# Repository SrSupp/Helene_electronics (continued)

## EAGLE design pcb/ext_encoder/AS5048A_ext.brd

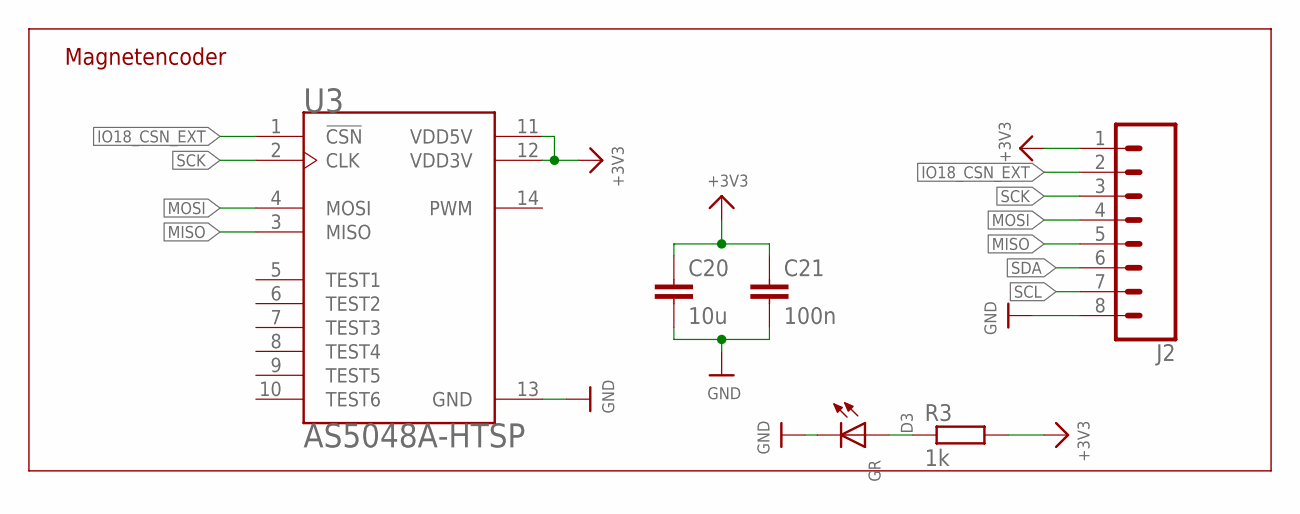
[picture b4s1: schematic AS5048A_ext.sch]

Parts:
C20: 10u; C0805
C21: 100n; C0805
D3: GR; CHIP-LED0805
J2: CONN_08BM08B-SRSS-TB; BM08B-SRSS-TB
R3: 1k; R0805
U3: AS5048A-HTSP; SOP65P640X120-14N

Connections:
+3V3: C20.1, C21.1, J2.1, R3.2, U3.11 (VDD5V), U3.12 (VDD3V)
GND: C20.2, C21.2, D3.C, J2.8, U3.13 (GND)
IO18_CSN_EXT: J2.2, U3.1 (!CSN)
MISO: J2.5, U3.3 (MISO)
MOSI: J2.4, U3.4 (MOSI)
unnamed: D3.A, R3.1
SCK: J2.3, U3.2 (CLK)
SCL: J2.7
SDA: J2.6

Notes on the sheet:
Magnetencoder

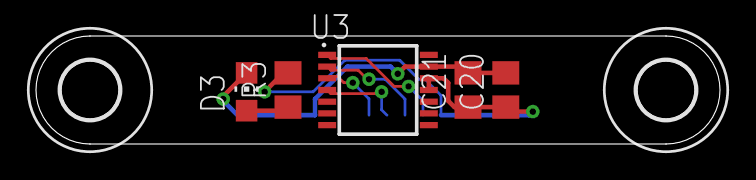
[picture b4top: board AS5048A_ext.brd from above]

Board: 2 copper layers, 38.0 x 6.0 mm, 8 parts (1 on the bottom side), 7 nets.

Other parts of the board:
U$1, U$2: 3,2

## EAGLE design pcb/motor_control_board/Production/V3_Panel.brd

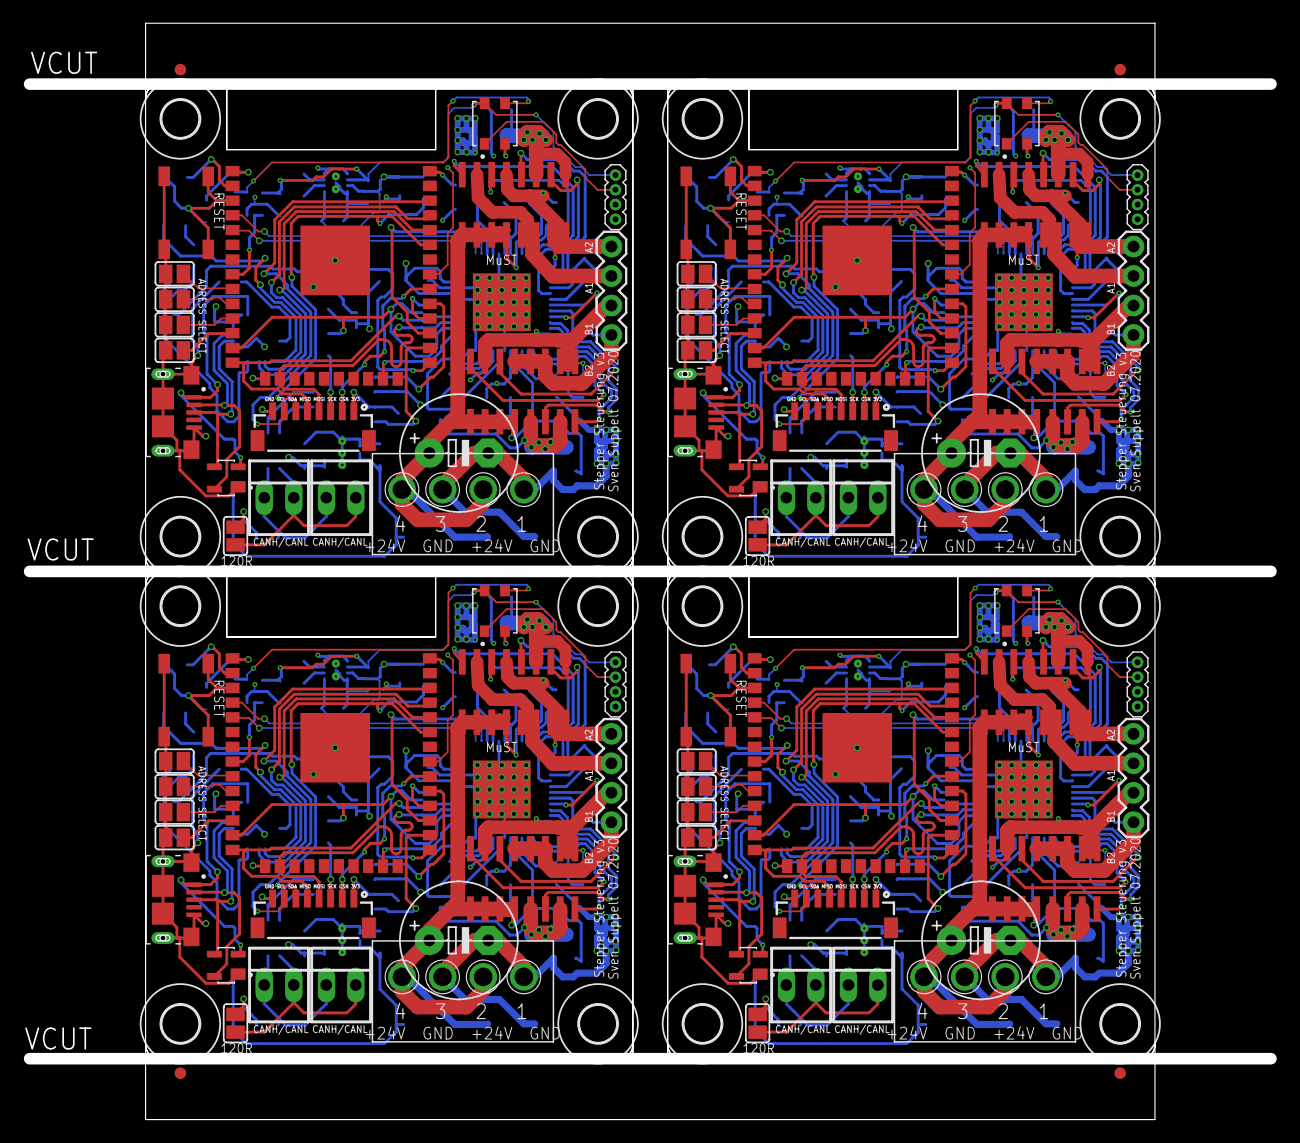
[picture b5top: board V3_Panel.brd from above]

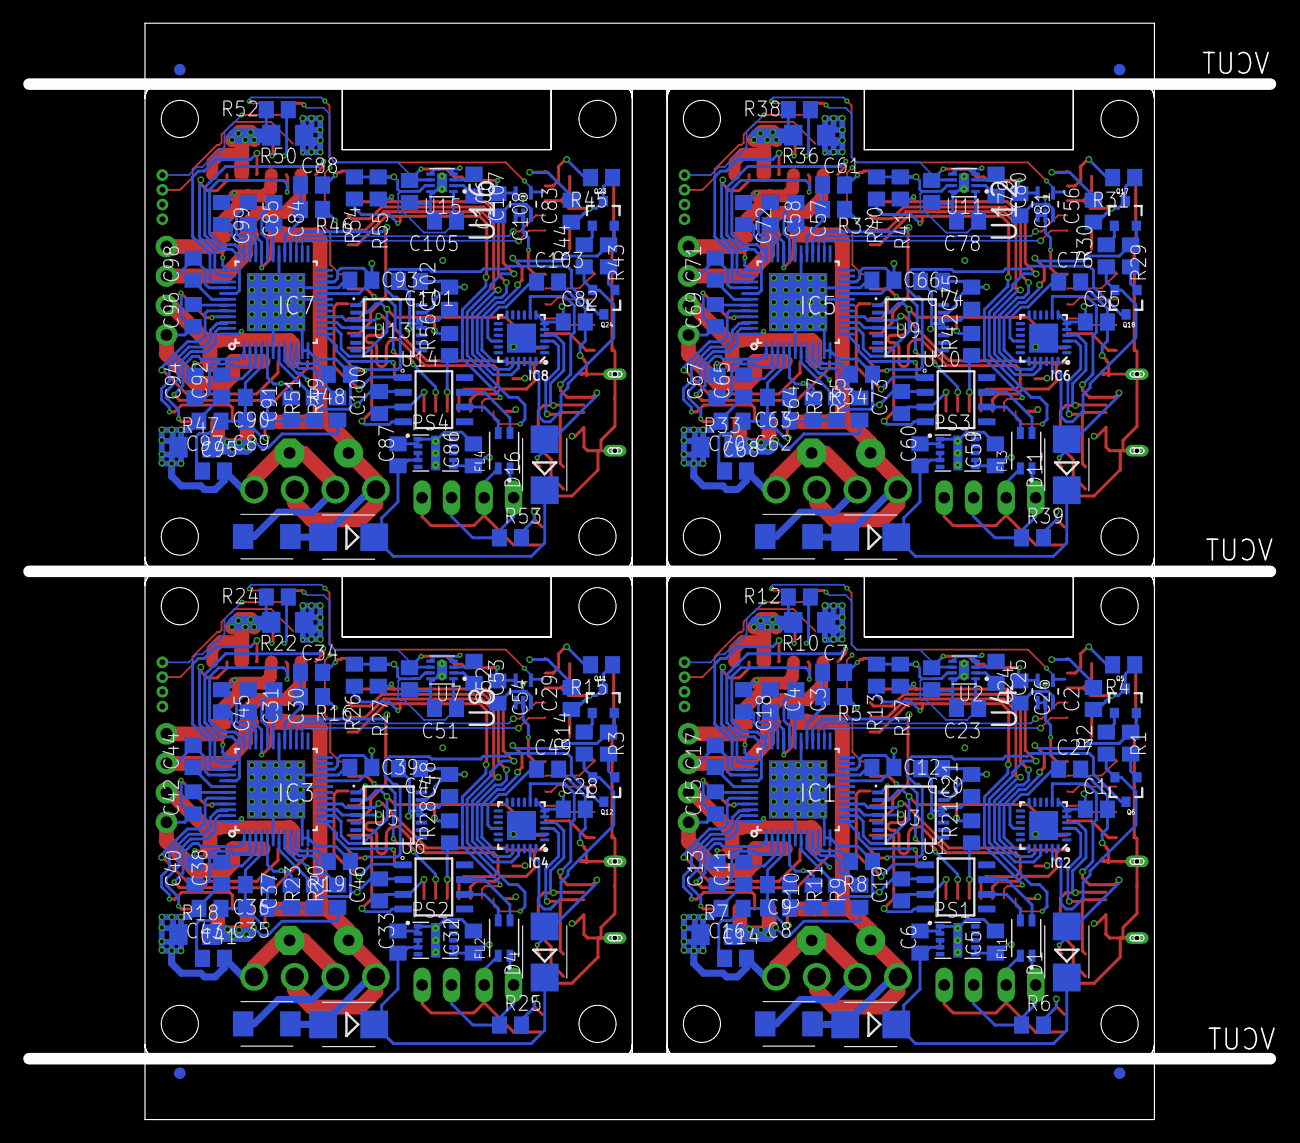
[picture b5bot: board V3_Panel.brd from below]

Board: 4 copper layers, 107.0 x 93.5 mm, 320 parts (216 on the bottom side), 296 nets.

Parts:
C1, C20, C28, C47, C55, C74, C82, C101: 10u; C0805
C2, C25, C29, C53, C56, C80, C83, C107: 1u; C0805
C3, C30, C57, C84: 22nF 100V; C0805
C4, C12, C13, C15, C17, C18, C19, C21, C26, C31, C39, C40, C42, C44, C45, C46, C48, C54, C58, C66, C67, C69, C71, C72, C73, C75, C81, C85, C93, C94, C96, C98, C99, C100, C102, C108: 100n; C0805
C5, C32, C59, C86: 47u; C0805
C6, C23, C24, C27, C33, C49, C51, C52, C60, C76, C78, C79, C87, C103, C105, C106: 4u7; C0805
C7, C14, C16, C34, C41, C43, C61, C68, C70, C88, C95, C97: 470n; C0805
C8, C9, C35, C36, C62, C63, C89, C90: 10u/50V; C0805
C10, C11, C37, C38, C64, C65, C91, C92: 2u2; C0805
C22, C50, C77, C104: E5-10,5
D1, D2, D4, D5, D11, D12, D16, D17: Schottky; SMB
D3, D9, D15, D20: 2659
D6, D7, D13, D18: SP0503BAHTG; SOT143
D8, D10, D14, D19: SMBJ30AQ-13-F; SMBJ
E$1, E$2, E$3, E$4, E$5, E$6, E$7, E$8: FIDUCIAL_1MM
FL1, FL2, FL3, FL4: DLW32SH220XK2L; FIL_DLW32SH110XK2L
IC1, IC3, IC5, IC7: TMC5160-TA; TQFP48-EP
IC2, IC4, IC6, IC8: CP2104; QFN24_4MM_SMSC
J1, J5, J9, J13: 1X04
J2, J6, J10, J14: BM08B-SRSS-TB
J3, J7, J11, J15: 1X04_1.27MM
J4, J8, J12, J16: 10118193-0001LF; FCI_10118193-0001LF
PS1, PS2, PS3, PS4: LMZM23600V3SILT; CONV_LMZM23600V3SILT
Q1, Q2, Q3, Q4, Q7, Q8, Q9, Q10, Q13, Q14, Q15, Q16, Q19, Q20, Q21, Q22: AO4882"; SOIC8
Q5, Q6, Q11, Q12, Q17, Q18, Q23, Q24: BC817; SOT23-3
R1, R2, R3, R14, R29, R30, R43, R44: 1k; R0805
R4, R13, R15, R17, R26, R27, R31, R40, R41, R45, R54, R55: 10k; R0805
R5, R16, R32, R46: 2R2; R0805
R6, R25, R39, R53: 120R; R0805
R7, R10, R18, R22, R33, R36, R47, R50: 0R075; R1206
R8, R9, R11, R12, R19, R20, R21, R23, R24, R28, R34, R35, R37, R38, R42, R48, R49, R51, R52, R56: 49R9; R0805
SJ1, SJ2, SJ3, SJ4, SJ5, SJ6, SJ7, SJ8, SJ9, SJ10, SJ11, SJ12, SJ13, SJ14, SJ15, SJ16, SJ17, SJ18, SJ19, SJ20: SJ
SW1, SW2, SW3, SW4: TL3342F160QG; SW_TL3342F160QG
U1, U6, U10, U14: SN65HVD232; SOIC127P600X175-8N
U2, U7, U11, U15: LM2775QDSGTQ1; SON50P200X200X80-9N
U3, U5, U9, U13: AS5048A-HTSP; SOP65P640X120-14N
U4, U8, U12, U16: 74LVC1G08; SOT65P210X110-5N
U$1, U$2, U$3, U$4, U$5, U$6, U$7, U$8, U$9, U$10, U$11, U$12, U$13, U$14, U$15, U$16: 3,2
X1, X8, X12, X16: PT11304HBBN; TYP184_FT
X2, X3, X9, X13: ESP32_WROOM32_SKINNY; WROOM32_SKINNY
X4, X5, X6, X7, X10, X11, X14, X15: 22-23-2021

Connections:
+3V1: C28.1, C32.1, C39.2, C46.1, C47.1, C48.1, C51.1, IC3.20, IC3.22, IC4.5, IC4.6, IC4.7, J6.1, PS2.6, PS2.7, R15.2, R26.2, R27.2, U5.11, U5.12, U6.3, U7.1, U7.4, U7.5, U7.7, X3.2
+3V2: C55.1, C59.1, C66.2, C73.1, C74.1, C75.1, C78.1, IC5.20, IC5.22, IC6.5, IC6.6, IC6.7, J10.1, PS3.6, PS3.7, R31.2, R40.2, R41.2, U9.11, U9.12, U10.3, U11.1, U11.4, U11.5, U11.7, X9.2
+3V3: C1.1, C5.1, C12.2, C19.1, C20.1, C21.1, C23.1, IC1.20, IC1.22, IC2.5, IC2.6, IC2.7, J2.1, PS1.6, PS1.7, R4.2, R13.2, R17.2, U1.3, U2.1, U2.4, U2.5, U2.7, U3.11, U3.12, X2.2
+3V4: C82.1, C86.1, C93.2, C100.1, C101.1, C102.1, C105.1, IC7.20, IC7.22, IC8.5, IC8.6, IC8.7, J14.1, PS4.6, PS4.7, R45.2, R54.2, R55.2, U13.11, U13.12, U14.3, U15.1, U15.4, U15.5, U15.7, X13.2
+5V: C10.2, IC1.5, R5.2
+5V1: C37.2, IC3.5, R16.2
+5V2: C64.2, IC5.5, R32.2
+5V3: C91.2, IC7.5, R46.2
+5V_LED: C24.1, C26.1, D3.4, J3.4, U2.6, U4.5
+5V_LED1: C52.1, C54.1, D9.4, J7.4, U7.6, U8.5
+5V_LED2: C79.1, C81.1, D15.4, J11.4, U11.6, U12.5
+5V_LED3: C106.1, C108.1, D20.4, J15.4, U15.6, U16.5
+12V: C11.2, IC1.3
+12V1: C38.2, IC3.3
+12V2: C65.2, IC5.3
+12V3: C92.2, IC7.3
+24V: C4.2, C8.2, C9.2, C14.1, C16.1, C22.+, D2.A, D10.C, IC1.4, IC1.33, Q1.5, Q1.6, Q1.7, Q1.8, Q3.5, Q3.6, Q3.7, Q3.8, X1.2, X1.4
+24V1: C31.2, C35.2, C36.2, C41.1, C43.1, C50.+, D5.A, D8.C, IC3.4, IC3.33, Q7.5, Q7.6, Q7.7, Q7.8, Q9.5, Q9.6, Q9.7, Q9.8, X8.2, X8.4
+24V2: C58.2, C62.2, C63.2, C68.1, C70.1, C77.+, D12.A, D14.C, IC5.4, IC5.33, Q13.5, Q13.6, Q13.7, Q13.8, Q15.5, Q15.6, Q15.7, Q15.8, X12.2, X12.4
+24V3: C85.2, C89.2, C90.2, C95.1, C97.1, C104.+, D17.A, D19.C, IC7.4, IC7.33, Q19.5, Q19.6, Q19.7, Q19.8, Q21.5, Q21.6, Q21.7, Q21.8, X16.2, X16.4
BMA1: C17.2, IC1.40, J1.2, Q3.3, Q4.5, Q4.6
BMA2: C18.1, IC1.37, J1.1, Q3.1, Q4.7, Q4.8
BMA3: C45.1, IC3.37, J5.1, Q9.1, Q10.7, Q10.8
BMA4: C44.2, IC3.40, J5.2, Q9.3, Q10.5, Q10.6
BMA5: C72.1, IC5.37, J9.1, Q15.1, Q16.7, Q16.8
BMA6: C71.2, IC5.40, J9.2, Q15.3, Q16.5, Q16.6
BMA7: C99.1, IC7.37, J13.1, Q21.1, Q22.7, Q22.8
BMA8: C98.2, IC7.40, J13.2, Q21.3, Q22.5, Q22.6
BMB1: C13.2, IC1.48, J1.3, Q1.3, Q2.5, Q2.6
BMB2: C15.1, IC1.45, J1.4, Q1.1, Q2.7, Q2.8
BMB3: C40.2, IC3.48, J5.3, Q7.3, Q8.5, Q8.6
BMB4: C42.1, IC3.45, J5.4, Q7.1, Q8.7, Q8.8
BMB5: C67.2, IC5.48, J9.3, Q13.3, Q14.5, Q14.6
BMB6: C69.1, IC5.45, J9.4, Q13.1, Q14.7, Q14.8
BMB7: C94.2, IC7.48, J13.3, Q19.3, Q20.5, Q20.6
BMB8: C96.1, IC7.45, J13.4, Q19.1, Q20.7, Q20.8
CA1: C17.1, IC1.42
CA2: C18.2, IC1.35
CA3: C44.1, IC3.42
CA4: C45.2, IC3.35
CA5: C71.1, IC5.42
CA6: C72.2, IC5.35
CA7: C98.1, IC7.42
CA8: C99.2, IC7.35
CANH: FL1.1, R6.1, X6.1, X7.1
CANH1: FL2.1, R25.1, X4.1, X5.1
CANH2: FL3.1, R39.1, X10.1, X11.1
CANH3: FL4.1, R53.1, X14.1, X15.1
CANL: FL1.4, SJ9.1, X6.2, X7.2
CANL1: FL2.4, SJ10.1, X4.2, X5.2
CANL2: FL3.4, SJ15.1, X10.2, X11.2
CANL3: FL4.4, SJ20.1, X14.2, X15.2
CB1: C13.1, IC1.2
CB2: C15.2, IC1.43
CB3: C42.2, IC3.43
CB4: C40.1, IC3.2
CB5: C69.2, IC5.43
CB6: C67.1, IC5.2
CB7: C96.2, IC7.43
CB8: C94.1, IC7.2
DTR: IC2.23, Q6.2, R2.1
DTR1: IC4.23, Q12.2, R14.1
DTR2: IC6.23, Q18.2, R30.1
DTR3: IC8.23, Q24.2, R44.1
GND: C1.2, C2.2, C5.2, C6.2, C7.2, C8.1, C9.1, C10.1, C11.1, C12.1, C14.2, C16.2, C19.2, C20.2, C21.2, C22.-, C23.2, C24.2, C26.2, C27.2, D3.2, D7.1, D10.A, IC1.6, IC1.11, IC1.12, IC1.19, IC1.21, IC1.30, IC1.49, IC2.2, IC2.THERM, J2.8, J3.1, J4.5, J4.S1, J4.S2, J4.S3, J4.S4, J4.S5, J4.S6, PS1.1, PS1.2, PS1.11, PS1.11_1, PS1.11_2, PS1.11_3, R7.1, R8.1, R10.1, R11.1, SJ5.1, SJ6.1, SJ7.1, SJ8.1, SW1.3, SW1.4, U1.2, U2.8, U2.9, U2.9_1, U2.9_2, U3.13, U4.3, X1.1, X1.3, X2.1, X2.15, X2.38, X2.P$1
GND1: C28.2, C29.2, C32.2, C33.2, C34.2, C35.1, C36.1, C37.1, C38.1, C39.1, C41.2, C43.2, C46.2, C47.2, C48.2, C49.2, C50.-, C51.2, C52.2, C54.2, D6.1, D8.A, D9.2, IC3.6, IC3.11, IC3.12, IC3.19, IC3.21, IC3.30, IC3.49, IC4.2, IC4.THERM, J6.8, J7.1, J8.5, J8.S1, J8.S2, J8.S3, J8.S4, J8.S5, J8.S6, PS2.1, PS2.2, PS2.11, PS2.11_1, PS2.11_2, PS2.11_3, R18.1, R19.1, R22.1, R23.1, SJ1.1, SJ2.1, SJ3.1, SJ4.1, SW2.3, SW2.4, U5.13, U6.2, U7.8, U7.9, U7.9_1, U7.9_2, U8.3, X3.1, X3.15, X3.38, X3.P$1, X8.1, X8.3
GND2: C55.2, C56.2, C59.2, C60.2, C61.2, C62.1, C63.1, C64.1, C65.1, C66.1, C68.2, C70.2, C73.2, C74.2, C75.2, C76.2, C77.-, C78.2, C79.2, C81.2, D13.1, D14.A, D15.2, IC5.6, IC5.11, IC5.12, IC5.19, IC5.21, IC5.30, IC5.49, IC6.2, IC6.THERM, J10.8, J11.1, J12.5, J12.S1, J12.S2, J12.S3, J12.S4, J12.S5, J12.S6, PS3.1, PS3.2, PS3.11, PS3.11_1, PS3.11_2, PS3.11_3, R33.1, R34.1, R36.1, R37.1, SJ11.1, SJ12.1, SJ13.1, SJ14.1, SW3.3, SW3.4, U9.13, U10.2, U11.8, U11.9, U11.9_1, U11.9_2, U12.3, X9.1, X9.15, X9.38, X9.P$1, X12.1, X12.3
GND3: C82.2, C83.2, C86.2, C87.2, C88.2, C89.1, C90.1, C91.1, C92.1, C93.1, C95.2, C97.2, C100.2, C101.2, C102.2, C103.2, C104.-, C105.2, C106.2, C108.2, D18.1, D19.A, D20.2, IC7.6, IC7.11, IC7.12, IC7.19, IC7.21, IC7.30, IC7.49, IC8.2, IC8.THERM, J14.8, J15.1, J16.5, J16.S1, J16.S2, J16.S3, J16.S4, J16.S5, J16.S6, PS4.1, PS4.2, PS4.11, PS4.11_1, PS4.11_2, PS4.11_3, R47.1, R48.1, R50.1, R51.1, SJ16.1, SJ17.1, SJ18.1, SJ19.1, SW4.3, SW4.4, U13.13, U14.2, U15.8, U15.9, U15.9_1, U15.9_2, U16.3, X13.1, X13.15, X13.38, X13.P$1, X16.1, X16.3
GPIO0: Q6.3, X2.25
GPIO1: Q12.3, X3.25
GPIO4: Q18.3, X9.25
GPIO6: Q24.3, X13.25
HA1: IC1.41, Q3.4
HA2: IC1.36, Q3.2
HA3: IC3.41, Q9.4
HA4: IC3.36, Q9.2
HA5: IC5.41, Q15.4
HA6: IC5.36, Q15.2
HA7: IC7.41, Q21.4
HA8: IC7.36, Q21.2
HB1: IC1.1, Q1.4
HB2: IC1.44, Q1.2
HB3: IC3.44, Q7.2
HB4: IC3.1, Q7.4
HB5: IC5.44, Q13.2
HB6: IC5.1, Q13.4
HB7: IC7.44, Q19.2
HB8: IC7.1, Q19.4
IO4_CANRX: U1.4, X2.26
IO4_CANRX1: U6.4, X3.26
IO4_CANRX2: U10.4, X9.26
IO4_CANRX3: U14.4, X13.26
IO5_CANTX: U1.1, X2.29
IO5_CANTX1: U6.1, X3.29
IO5_CANTX2: U10.1, X9.29
IO5_CANTX3: U14.1, X13.29
IO15_CSN_TMC: IC1.13, X2.23
IO15_CSN_TMC1: IC3.13, X3.23
IO15_CSN_TMC2: IC5.13, X9.23
IO15_CSN_TMC3: IC7.13, X13.23
IO16_DRV_ENN: IC1.28, X2.27
IO16_DRV_ENN1: IC3.28, X3.27
IO16_DRV_ENN2: IC5.28, X9.27
IO16_DRV_ENN3: IC7.28, X13.27
IO17_CSN_AS: U3.1, X2.28
IO17_CSN_AS1: U5.1, X3.28
IO17_CSN_AS2: U9.1, X9.28
IO17_CSN_AS3: U13.1, X13.28
IO18_CSN_EXT: J2.2, X2.30
IO18_CSN_EXT1: J6.2, X3.30
IO18_CSN_EXT2: J10.2, X9.30
IO18_CSN_EXT3: J14.2, X13.30
IO19_ALG_OUT: J3.2, X2.31
IO19_ALG_OUT1: J7.2, X3.31
IO19_ALG_OUT2: J11.2, X9.31
IO19_ALG_OUT3: J15.2, X13.31
IO25_ADR1: SJ6.2, X2.10
IO25_ADR2: SJ2.2, X3.10
IO25_ADR3: SJ12.2, X9.10
IO25_ADR4: SJ17.2, X13.10
IO26_ADR1: SJ3.2, X3.11
IO26_ADR2: SJ7.2, X2.11
IO26_ADR3: SJ13.2, X9.11
IO26_ADR4: SJ18.2, X13.11
IO27_ADR1: SJ4.2, X3.12
IO27_ADR2: SJ14.2, X9.12
IO27_ADR3: SJ8.2, X2.12
IO27_ADR4: SJ19.2, X13.12
IO32_NEOPIXEL_3V1: U8.1, U8.2, X3.8
IO32_NEOPIXEL_3V2: U12.1, U12.2, X9.8
IO32_NEOPIXEL_3V3: U4.1, U4.2, X2.8
IO32_NEOPIXEL_3V4: U16.1, U16.2, X13.8
IO33_ADR0: SJ5.2, X2.9
IO33_ADR1: SJ1.2, X3.9
IO33_ADR2: SJ11.2, X9.9
IO33_ADR3: SJ16.2, X13.9
LA1: IC1.39, Q4.4
LA2: IC1.38, Q4.2
LA3: IC3.38, Q10.2
LA4: IC3.39, Q10.4
LA5: IC5.38, Q16.2
LA6: IC5.39, Q16.4
LA7: IC7.38, Q22.2
LA8: IC7.39, Q22.4
LB1: IC1.47, Q2.4
LB2: IC1.46, Q2.2
LB3: IC3.47, Q8.4
LB4: IC3.46, Q8.2
LB5: IC5.47, Q14.4
LB6: IC5.46, Q14.2
LB7: IC7.47, Q20.4
LB8: IC7.46, Q20.2
MISO: IC1.16, J2.5, U3.3, X2.14
MISO1: IC3.16, J6.5, U5.3, X3.14
MISO2: IC5.16, J10.5, U9.3, X9.14
MISO3: IC7.16, J14.5, U13.3, X13.14
MOSI: IC1.15, J2.4, U3.4, X2.16
MOSI1: IC3.15, J6.4, U5.4, X3.16
MOSI2: IC5.15, J10.4, U9.4, X9.16
MOSI3: IC7.15, J14.4, U13.4, X13.16
unnamed: C25.1, U2.3
unnamed: C6.1, D1.C, D2.C, PS1.3, PS1.4
unnamed: C3.2, IC1.31
unnamed: C3.1, IC1.32
unnamed: C4.1, IC1.34
unnamed: C25.2, U2.2
unnamed: C7.1, IC1.29, R5.1
unnamed: FL1.2, U1.7
unnamed: Q4.1, Q4.3, R10.2, R12.1
unnamed: Q2.1, Q2.3, R7.2, R9.1
unnamed: FL1.3, U1.6
unnamed: Q5.1, R2.2
unnamed: Q6.1, R1.2
unnamed: Q11.1, R14.2
unnamed: D3.3, U4.4
unnamed: R6.2, SJ9.2
unnamed: Q12.1, R3.2
unnamed: C30.2, IC3.31
unnamed: C30.1, IC3.32
unnamed: C31.1, IC3.34
unnamed: J2.3, R21.1
unnamed: C27.1, IC2.16
unnamed: C34.1, IC3.29, R16.1
unnamed: Q8.1, Q8.3, R18.2, R20.1
unnamed: Q10.1, Q10.3, R22.2, R24.1
unnamed: R25.2, SJ10.2
unnamed: C33.1, D4.C, D5.C, PS2.3, PS2.4
unnamed: J6.3, R28.1
unnamed: C49.1, IC4.16
unnamed: C53.1, U7.3
unnamed: C53.2, U7.2
unnamed: D9.3, U8.4
unnamed: FL2.2, U6.7
unnamed: FL2.3, U6.6
unnamed: Q17.1, R30.2
unnamed: Q18.1, R29.2
unnamed: C57.2, IC5.31
unnamed: C57.1, IC5.32
unnamed: C58.1, IC5.34
unnamed: C61.1, IC5.29, R32.1
unnamed: Q14.1, Q14.3, R33.2, R35.1
unnamed: Q16.1, Q16.3, R36.2, R38.1
unnamed: R39.2, SJ15.2
unnamed: C60.1, D11.C, D12.C, PS3.3, PS3.4
unnamed: J10.3, R42.1
unnamed: C76.1, IC6.16
unnamed: C80.1, U11.3
unnamed: C80.2, U11.2
unnamed: D15.3, U12.4
unnamed: FL3.2, U10.7
unnamed: FL3.3, U10.6
unnamed: Q23.1, R44.2
unnamed: Q24.1, R43.2
unnamed: C84.2, IC7.31
unnamed: C84.1, IC7.32
unnamed: C85.1, IC7.34
unnamed: C88.1, IC7.29, R46.1
unnamed: Q20.1, Q20.3, R47.2, R49.1
unnamed: Q22.1, Q22.3, R50.2, R52.1
unnamed: R53.2, SJ20.2
unnamed: C87.1, D16.C, D17.C, PS4.3, PS4.4
unnamed: J14.3, R56.1
unnamed: C103.1, IC8.16
unnamed: C107.1, U15.3
unnamed: C107.2, U15.2
unnamed: D20.3, U16.4
unnamed: FL4.2, U14.7
unnamed: FL4.3, U14.6
NEO_OUT: D3.1, J3.3
NEO_OUT1: D9.1, J7.3
NEO_OUT2: D15.1, J11.3
NEO_OUT3: D20.1, J15.3
RESET: C2.1, Q5.3, R4.1, SW1.1, SW1.2, X2.3
RESET1: C29.1, Q11.3, R15.1, SW2.1, SW2.2, X3.3
RESET2: C56.1, Q17.3, R31.1, SW3.1, SW3.2, X9.3
RESET3: C83.1, Q23.3, R45.1, SW4.1, SW4.2, X13.3
RTS: IC2.19, Q5.2, R1.1
RTS1: IC4.19, Q11.2, R3.1
RTS2: IC6.19, Q17.2, R29.1
RTS3: IC8.19, Q23.2, R43.1
RXD0: IC2.21, X2.34
RXD1: IC4.21, X3.34
RXD2: IC6.21, X9.34
RXD3: IC8.21, X13.34
SCK: IC1.14, R21.2, U3.2, X2.13
SCK1: IC3.14, R28.2, U5.2, X3.13
SCK2: IC5.14, R42.2, U9.2, X9.13
SCK3: IC7.14, R56.2, U13.2, X13.13
SCL: J2.7, R17.1, X2.36
SCL1: J6.7, R27.1, X3.36
SCL2: J10.7, R41.1, X9.36
SCL3: J14.7, R55.1, X13.36
SDA: J2.6, R13.1, X2.33
SDA1: J6.6, R26.1, X3.33
SDA2: J10.6, R40.1, X9.33
SDA3: J14.6, R54.1, X13.33
SRAH: IC1.8, R12.2
SRAH1: IC3.8, R24.2
SRAH2: IC5.8, R38.2
SRAH3: IC7.8, R52.2
SRAL: IC1.7, R11.2
SRAL1: IC3.7, R23.2
SRAL2: IC5.7, R37.2
SRAL3: IC7.7, R51.2
SRBH: IC1.9, R9.2
SRBH1: IC3.9, R20.2
SRBH2: IC5.9, R35.2
SRBH3: IC7.9, R49.2
SRBL: IC1.10, R8.2
SRBL1: IC3.10, R19.2
SRBL2: IC5.10, R34.2
SRBL3: IC7.10, R48.2
TMC_DIAG0: IC1.26, X2.5
TMC_DIAG1: IC1.27, X2.4
TMC_DIAG2: IC3.27, X3.4
TMC_DIAG3: IC3.26, X3.5
TMC_DIAG4: IC5.27, X9.4
TMC_DIAG5: IC5.26, X9.5
TMC_DIAG6: IC7.27, X13.4
TMC_DIAG7: IC7.26, X13.5
TXD0: IC2.20, X2.35
TXD1: IC4.20, X3.35
TXD2: IC6.20, X9.35
TXD3: IC8.20, X13.35
USBD+: D7.3, IC2.3, J4.3
USBD+1: D6.3, IC4.3, J8.3
USBD+2: D13.3, IC6.3, J12.3
USBD+3: D18.3, IC8.3, J16.3
USBD-: D7.4, IC2.4, J4.2
USBD-1: D6.4, IC4.4, J8.2
USBD-2: D13.4, IC6.4, J12.2
USBD-3: D18.4, IC8.4, J16.2
VBUS: D1.A, D7.2, IC2.8, J4.1
VBUS1: D4.A, D6.2, IC4.8, J8.1
VBUS2: D11.A, D13.2, IC6.8, J12.1
VBUS3: D16.A, D18.2, IC8.8, J16.1

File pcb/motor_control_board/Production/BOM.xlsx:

|  |  | Motorsteuerung V3 BOM
Item # | *Designator | *Qty | Manufacturer | *Mfg Part # | Description / Value | *Package/Footprint | Type | Your Instructions / Notes
1 | C1, C20 | 2 | Murata | GRM21BR6YA106KE43L | 10uF 0805 min.5V | 0805 | SMD
2 | C2, C25 | 2 | KEMET | C0805C105K4RAC7210 | 1uF 0805 min. 5V | 0805 | SMD
3 | C3 | 1 | Yageo | CC0805KRX7R0BB223 | 22nF 0805 100V | 0805 | SMD
4 | C4, C12, C13, C15, C17, C18, C19, C21, C26 | 9 | KEMET | C0805C104J5RACAUTO | 100nF 0805 | 0805 | SMD
5 | C5 | 1 | Taiyo Yuden | JMK212BJ476MG-T | 47uF 0805 min 4V | 0805 | SMD
6 | C6, C23, C24, C27 | 4 | Taiyo Yuden | UMK212BBJ475MG-T | 4,7uF 0805 min 5V | 0805 | SMD
7 | C7, C14, C16 | 3 | KEMET | C0805C474K5RAC7210 | 470nF 0805 min 25V | 0805 | SMD
8 | C8, C9 | 2 | Murata | GRM21BR6YA106KE43L | 10uF 0805 min 25V | 0805 | SMD
9 | C10, C11 | 2 | Taiyo Yuden | UMK212ABJ225KG-T | 2,2uF 0805 min 12V | 0805 | SMD
10 | C22 | 1 | Do not equip | Do not equip | Do not equip | Do not equip | THT | Do not equip
11 | R1, R2 | 2 | Yageo | RC0805FR-071KL | 1k 0805 | 0805 | SMD
12 | R4, R13, R17 | 3 | Yageo | RC0805JR-0710KL | 10k 0805 | 0805 | SMD
13 | R5 | 1 | CR0805-J/-2R2ELF | Bourns | 2,2 Ohm 0805 | 0805 | SMD
14 | R6 | 1 | Yageo | RC0805FR-07120RL | 120 Ohm 0805 | 0805 | SMD
15 | R7, R10 | 2 | Yageo | RL1206FR-070R075L | 75mOhm 1206 | 1206 | SMD | Messshunt
16 | R8, R9, R11, R12, R21 | 5 | Panasonic | ERA-6AEB49R9V | 49,9 Ohm 0805 | 0805 | SMD
17 | D1, D2 | 2 | Multicomp | SS34A | SMB Shottky Diode | SMB | SMD
18 | D3 | 1 | Adafruit Industries | 2659 | 2659 Adafruit LED | 2659 | SMD
19 | D7 | 1 | Littlefuse | SP0503BAHTG | USB ESD Schutz | SOT143 | SMD
20 | D10 | 1 | Diodes Inc. | SMBJ30AQ-13-F | TVS Diode | SMBJ | SMD
21 | IC1 | 1 | Trinamic | TMC5160-TA-T | Motortreiber IC | TQFP48-EP | SMD
22 | IC2 | 1 | Solicon Labs | CP2104-F03-GM | USB Seriell Wandler | QFN24_4MM_SMSC | SMD
23 | J1 | 1 | Do not equip | Do not equip | Do not equip | Do not equip | THT
24 | J2 | 1 | JST | BM08B-SRSS-TB(LF)(SN) | 8 Port SMD stehende Buchse |  | SMD
25 | J3 | 1 | Do not equip | Do not equip | Do not equip | Do not equip | THT
27 | J4 | 1 | Amphenol FCI | 10118193-0001LF | USB-Stecker 5P MICRO USB TYPE B RECEPTACLE W/ PEGS | FCI_10118193-0001LF | SMD
28 | PS1 | 1 | Texas Instruments | LMZM23600V3SILR | 3,3V Spannungswandler |  | SMD
29 | Q1, Q2, Q3, Q4 | 4 | Alpha&Omega | AO4882 | Dual N-Ch Mosfet | SOIC8 | SMD
30 | Q5, Q6 | 2 | ON Semiconductor | BC817-16LT1G | NPN Transistor | SOT23-3 | SMD
31 | SJ1, SJ2 | 2 | Do not equip | Do not equip | Do not equip | Do not equip | SMD | Do not equip
32 | SJ5, SJ6, SJ7, SJ8, SJ9 | 5 | Do not equip | Do not equip | Do not equip | Do not equip | SMD | Do not equip
33 | SW1 | 1 | E-Switch | TL3342F160QG | Taster |  | SMD
34 | U1 | 1 | Texas Instruments | SN65HVD232DR | Can Treiber | SOIC127P600X175-8N | SMD
35 | U2 | 1 | Texas Instruments | LM2775QDSGTQ1 | 3,3V zu 5v | SON50P200X200X80-9N | SMD
36 | U3 | 1 | ams | AS5048A-HTSP-500 | Magnetencoder | SOP65P640X120-14N | SMD
37 | U4 | 1 | Nexperia | 74HCT1G08GW,125 | And Gate | SOT65P210X110-5N | SMD
38 | X1 | 1 | Do not equip | Do not equip | Do not equip | Do not equip | THT | Do not equip
39 | X2 | 1 | Espressif Systems | ESP32-WROOM-32 | Microprozessor |  | SMD
40 | X6, X7 | 2 | Do not equip | Do not equip | Do not equip | Do not equip | THT | Do not equip
41 | FL1 | 1 | Murata | DLW32SH220XK2L | Gleichtaktdrosseln / Filter 1210 80VDC 22uH 250mA AEC-Q200 | 1210 | SMD

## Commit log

2020-07-21 Added the existing stuff
2020-07-21 -pio
2020-08-22 Pictures and Readme
2020-08-22 Changed folder structure
2020-08-28 Changed transmissions
2020-08-29 Added Getactualpos, Fixed the Nullpunktfahrt and many bug fixes
2020-08-29 Bug fixes
2020-08-29 Pictures
2020-09-01 Fixed BOM
2020-09-02 Fixed Acceleration
2020-09-03 Fixed Motor Currents, Added DONU, GERA
2020-09-04 Production Files
2020-09-12 Fixed the calibration, added some SCPI functions
2020-09-13 Error Codes
2020-09-14 Slower refresh rate
2020-09-22 Label motor control board
2020-09-27 Many small changes
2020-09-27 Video
2020-10-22 Added optional external H-Bridge
2021-04-20 update roslib
2021-04-26 add servo library, use reserved topic to control servo through GPIO
2021-05-16 Added end-effector pcb and example code. Also fixed the gitignore
2021-05-16 Added a topic to which measurment data can be published into
2021-05-16 I fucked it up. Firmware is fixed now // Typo!
2021-05-20 End effector code update
2025-02-27 Create LICENSE
2025-06-17 Replaced Level Shifter for LEDs. Thanks to Yu-Lien Fang for noticing!
2025-06-17 Also changed PDF of schematics
